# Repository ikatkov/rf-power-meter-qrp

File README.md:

# RF Power Meter QRP

This microcontroller-based RF power meter is tailored for Ham QRP, capable of measuring up to 6W. It offers power readings in two formats:

1. Milliwatts (mW) – displayed as a 4-digit value without decimals.
1. Decibel-milliwatts (dBm) – shown with one decimal place. Since the display lacks a dot, the reading appears as a 3-digit number (e.g., "123" represents 12.3 dBm).
1. Accuracy 0.4% @ 6W (+-25mW), 5% @ 10mW (+-0.5mW)

## Features

- Up to 6W RF power meter, assumes sin wave
- Peak power hold mode
- Compensated frequency resonse, less that 1.03 SWR 2-50MHz
- Power measurements in dBm and Watts on 4-digit LED display
- Support for multiple Ham frequency bands (3.7-50MHz)
- Calibrated and uses polynomial curve fitting for accurate measurements. Manually set frequency band in settings.
- Battery voltage monitoring and auto power-off after 5 minutes of inactivity. Press any button to reset.
- Vent holes on plastic enclosure have filters made of surgical mask fiber (anti dust for field operation)

## 2MHz - 50MHz

## 2MHz - 175MHz

## Hardware

Schematic - [PDF](schematic.pdf)

- Arduino-compatible microcontroller
- 4-digit+MHz symbol LED display (salavged from a car FM transmitter)
- RF didode detector circuit
- Power latch circuit for MCU driven turn off
- Buzzer for audio feedback
- External precision voltage reference 

## Usage

- **To Power On**: Flip the main (storage mode) switch to ON. Press and hold the OK button (lower) to power on. Device starts with battery voltage displayed, followed by the currently selected frequency band. 

- **Info Button** (top):
  - Single click: Toggle between dBm/Watts
  - Double click: Enter measurement mode selection. Use the same button to switch between modes **continious** (default) vs **hold peak** mode. Use OK button to confirm when done.
  - Long press: Enter frequency band selection. Use the same button to cycle through bands.Use OK button to confirm when done.
- **OK Button** (bottom):
  - Single click: When in main screen - resets to zero, in menu screens confirms selection and exit to the main screen.
  - Long press (2s): Powers off

## Technical Specifications

- Calibrated for Ham frequency bands: 3.7MHz, 7.2MHz, 14.2MHz, 18MHz, 21MHz, 24MHz, 28MHz, 50MHz 
- Accuracy 0.4% @ 6W (+-25mW), 5% @ 10mW (+-0.5mW)
- Min power level: 2mW (3dBm)
- Max power level: 6.3W (38dBm) in short burst, 4W continious
- Not temperature compensated
- Internal 500mAh battery, USB charged
- When powered off, 200uA current consumption. You can use storage mode switch to disconnect internal battery competely.

## Notes

Since it's a diode detector the only thing it can measure is peak voltage. Code inside assumes that input RF signal is a pure sine wave to make RF power calculations. 

### Frequency compensation

Leads and connector and other stray inductance skew 50Ω impedance, one good way to compensate is to add adjustanble shunt capacitance. Use VNA to adjust after pcb assembly.

[ltspice file](ltspice/qrt-rf-power-meter-shunt-cap-compensation.asc)

### DC supply filtering

Internal battery is nominal 3.7V, but the salvaged LCD screen needs 5V. There is boost DC-DC converter that gives 200mV ripple. There are two filters - one right after the converter, this goes to MCU. There is another one just before reference voltage goes to Aref pin.

[ltspice file](ltspice/power-ripple-filter.asc)

### Interface

The Salvaged FM LCD screen has two buttons, so I had to fallback to "click" vs "double-click" vs "long click" technique. The same button function differently depending in which mode device currently is - "main screen" vs "settings"

The screen itself has 4 digits and one dot. The dot is connected to "MHz" symbol. They always lit together.
Although I needed the dot for measurements, for example for dBms, I decided that showing "12.3 MHz" and claiming that this is "12.3 dBm" is rather akward. So the reading appears as a 3-digit number e.g. "123" represents 12.3 dBm. Watts reading always appear as 4 digit numbers with leading zeros as mW, "0123" reading represents 123mW. The dot and the "MHz" symbol come very handy when displaying frequency band. This setting is used to select which callibration curve to apply to the actual measurement.

Here is transition diagram:

```
                 ┌───────────────┐                   ┌─────────────┐
                 │ Cycle through ├───OK─button───────►  Saves to   │
                 │   Ham bands   │    click          │    NVRAM    │
                 └──────▲────────┘                   └───────┬─────┘
                        │                                    │      
                   info button                               │      
                     click                                   │      
                        │                                    │      
                 ┌──────┴────────┐                           │      
                 │Frequency band │                           │      
                 │  selection    │                           │      
                 │   screen      │                           │      
                 └───────────────┘                           │      
                       ▲ ▲                                   │      
                       │ │                                   │      
                       │ │                                   │      
                    info button                              │      
        ┌───────────long press─────────┐                     │      
        │                              │                     │      
        │                              │                     │      
        │                              │                     │      
┌───────┴───────┐              ┌───────┴───────┐             │      
│  Main screen  ├─info─button─►│  Main screen  │◄────────────┘      
│    mWatts     │◄──click──────┤     dBm       │◄────────────┐      
└───────┬───────┘              └───────┬───────┘             │      
        │                              │                     │      
        │                              │                     │      
        │                              │                     │      
        └──────────info button─────────┘                     │      
                   double│click                              │      
                      │  │                                   │      
                ┌─────▼──▼─────┐         When in the         │      
                │  Continious  │        "Hold Peak mode"     │      
                │     vs       │         display blinks      │      
                │  Hold peak   │                             │      
                └───────┬──────┘                             │      
                        │                                    │      
                   info button                               │      
                     click                                   │      
                        │                                    │      
                ┌───────▼─────────┐                          │      
                │  Cycle through  ├────OK─button─────────────┘      
                │    two modes    │     click                       
                └─────────────────┘                                                                                  
```                   

In any mode, long press on the "OK" button turns power off.

## License

[MIT License](LICENSE)

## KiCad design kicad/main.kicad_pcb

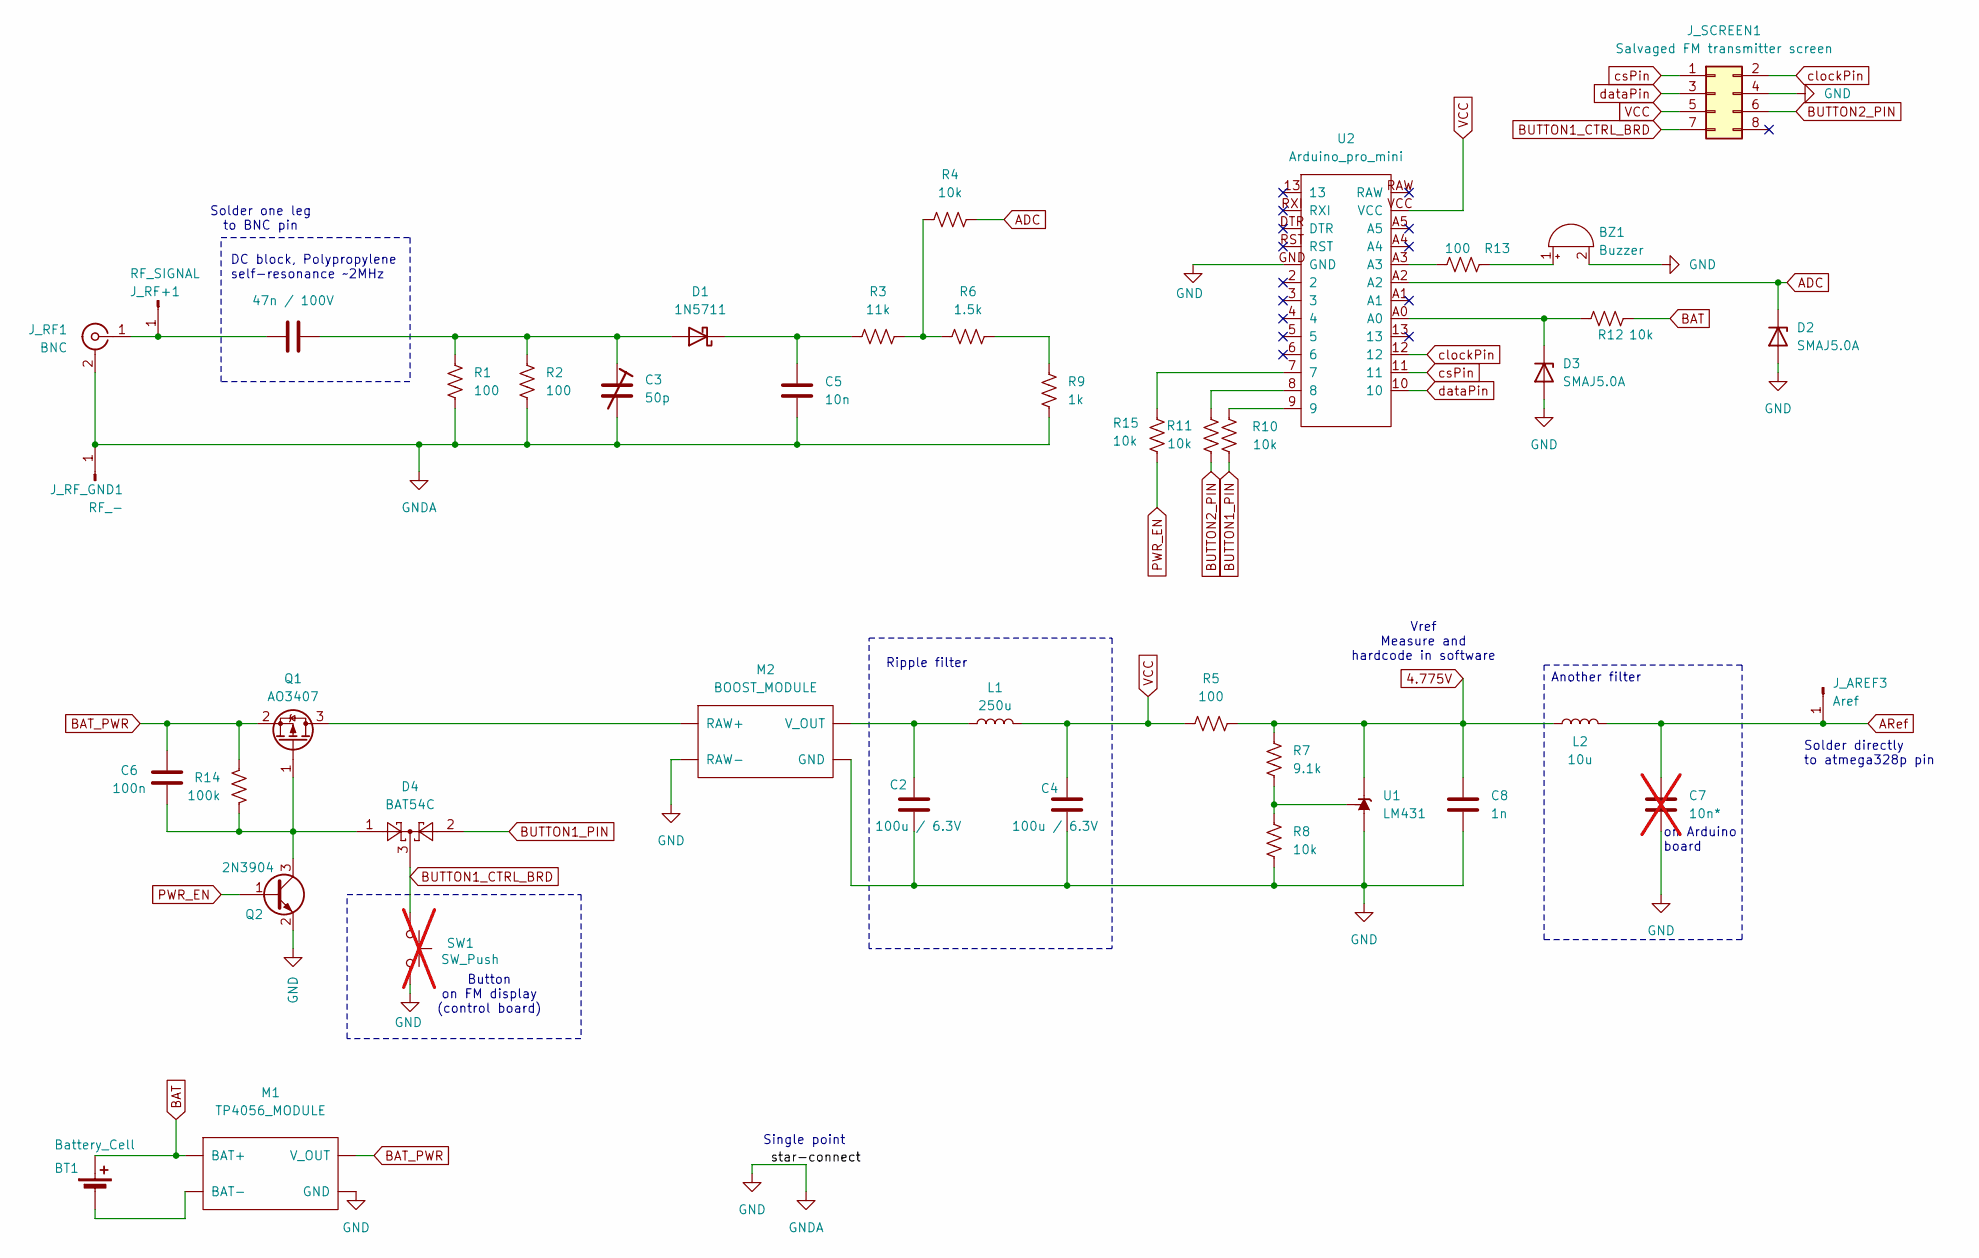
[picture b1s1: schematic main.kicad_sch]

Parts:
BT1: Battery_Cell
BZ1: Buzzer; Buzzer_12x9.5RM7.6
C1: 47n / 100V; C_Disc_D8.0mm_W2.5mm_P5.00mm
C2, C4: 100u / 6.3V; C_1206_3216Metric
C3: 50p; trimmer-capacitor-JML06
C5: 10n; C_1206_3216Metric
C6: 100n; C_1206_3216Metric
C7: 10n*; C_1206_3216Metric; not fitted
C8: 1n; C_1206_3216Metric
D1: 1N5711; D_DO-35_SOD27_P7.62mm_Horizontal
D2, D3: SMAJ5.0A; D_SMA
D4: BAT54C; SOT-23
J_AREF3: Aref; SolderWire-0.25sqmm_1x01_D0.65mm_OD2mm
J_RF1: BNC; SolderWire-1.5sqmm_1x01_D1.7mm_OD3.9mm
J_RF+1: RF_SIGNAL; SolderWire-1.5sqmm_1x01_D1.7mm_OD3.9mm
J_RF_GND1: RF_-; SolderWire-1.5sqmm_1x01_D1.7mm_OD3.9mm
J_SCREEN1: Salvaged FM transmitter screen; IDC-Header_2x04_P2.54mm_Vertical
L1: 250u; L_Bourns_SRN6045TA
L2: 10u; L_0805_2012Metric
M1: TP4056_MODULE; TP4056-18650
M2: BOOST_MODULE; boost-module
Q1: AO3407; SOT-23
Q2: 2N3904; SOT-23
R1, R2: 100; R_Axial_DIN0922_L20.0mm_D9.0mm_P25.40mm_Horizontal
R3: 11k; R_0805_2012Metric
R4, R8, R10, R11, R12, R15: 10k; R_0805_2012Metric
R5, R13: 100; R_0805_2012Metric
R6: 1.5k; R_0805_2012Metric
R7: 9.1k; R_0805_2012Metric
R9: 1k; R_0805_2012Metric
R14: 100k; R_0805_2012Metric
SW1: SW_Push; SW_Tactile_SPST_Angled_PTS645Vx31-2LFS; not fitted
U1: LM431; TO-92L_HandSolder
U2: Arduino_pro_mini; ARDUINO_PRO_MINI_NO_A5

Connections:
4.775V: C8.1, L2.1, R5.1, R7.1, U1.3 (K)
ADC: D2.1 (K), R4.2, U2.A2
ARef: C7.1, J_AREF3.1, L2.2
BAT: BT1.1 (+), M1.5 (BAT+), R12.1
BAT_PWR: C6.2, M1.3 (V_OUT), Q1.2 (S), R14.2
BUTTON1: D4.2, R10.2
BUTTON1_PIN: D4.3, J_SCREEN1.7, SW1.1
BUTTON2: J_SCREEN1.6, R11.2
GND: BZ1.2 (-), C2.2, C3.2, C4.2, C5.2, C7.2, C8.2, D2.2 (A), D3.2 (A), J_RF1.2 (Ext), J_RF_GND1.1, J_SCREEN1.4, M1.4 (GND), M2.1 (RAW-), M2.4 (GND), Q2.2 (E), R1.2, R2.2, R8.2, R9.2, SW1.2, U1.2 (A), U2.GND
unnamed: BZ1.1 (+), R13.1
unnamed: C1.2, C3.1, D1.2 (A), R1.1, R2.1
unnamed: C5.1, D1.1 (K), R3.1
unnamed: D3.1 (K), R12.2, U2.A0
unnamed: C1.1, J_RF1.1 (In), J_RF+1.1
unnamed: BT1.2 (-), M1.6 (BAT-)
unnamed: M2.2 (RAW+), Q1.3 (D)
unnamed: C2.1, L1.1, M2.3 (V_OUT)
unnamed: C6.1, D4.1, Q1.1 (G), Q2.3 (C), R14.1
unnamed: R3.2, R4.1, R6.2
unnamed: R6.1, R9.1
unnamed: R10.1, U2.9
unnamed: R11.1, U2.8
unnamed: R13.2, U2.A3
unnamed: R15.2, U2.7
unnamed: R7.2, R8.1, U1.1 (REF)
PWR_EN: Q2.1 (B), R15.1
VCC: C4.1, J_SCREEN1.5, L1.2, R5.2, U2.VCC
clockPin: J_SCREEN1.2, U2.12
csPin: J_SCREEN1.1, U2.11
dataPin: J_SCREEN1.3, U2.10

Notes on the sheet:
Ripple filter
Vref Measure and hardcode in software
Another filter
DC block, Polypropylene self-resonance ~2MHz
Button on FM display (control board)
Solder one leg to BNC pin
Single point
on Arduino board
Solder directly to atmega328p pin

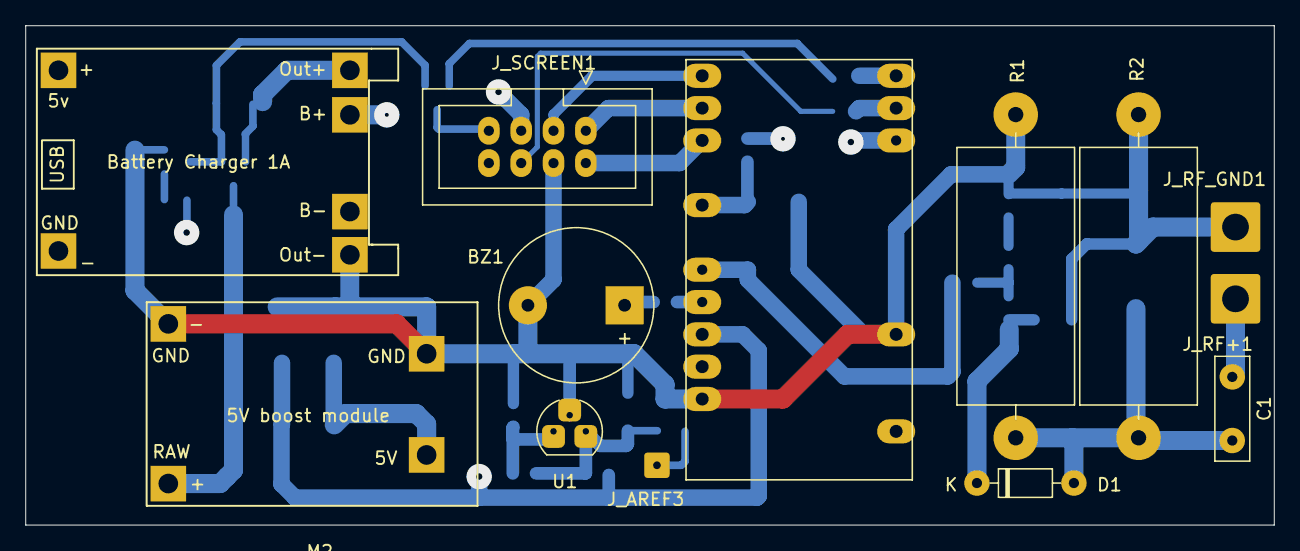
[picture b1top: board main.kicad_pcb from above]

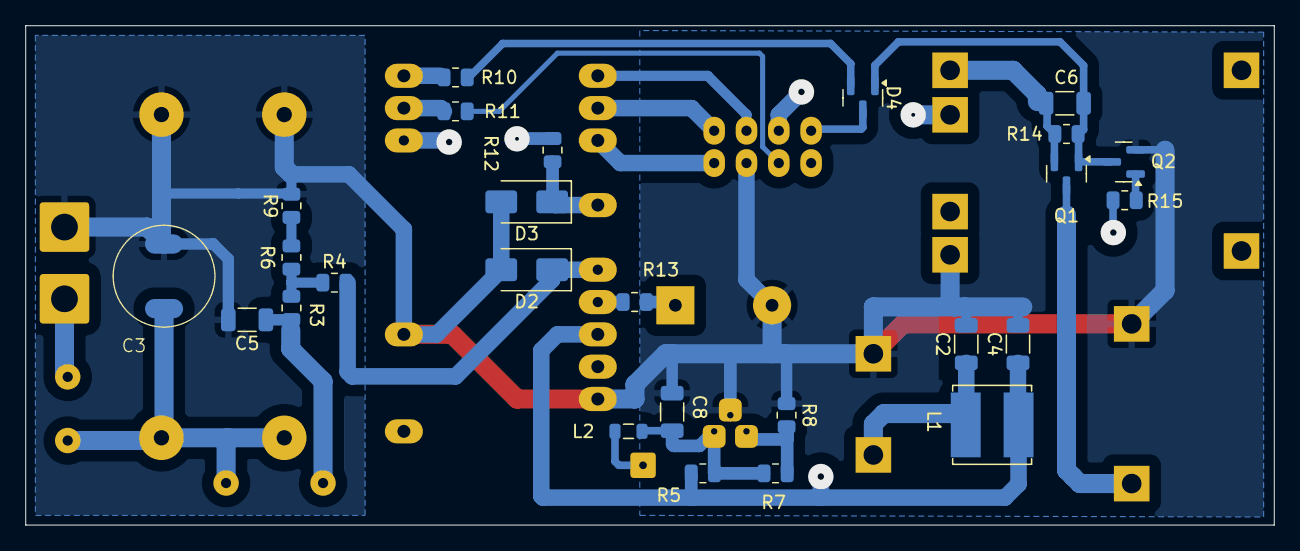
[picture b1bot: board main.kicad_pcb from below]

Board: 4 copper layers, 98.1 x 39.2 mm, 39 parts (26 on the bottom side), 29 nets.

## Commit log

2024-12-30 feat: Initial commit
2024-12-31 Add 3d model for enclosure
2024-12-31 Add python pre-req
2025-01-03 docs: clean up schematic and export to pdf and images
2025-01-03 docs: formatting
2025-01-03 docs: Update wording
2025-01-04 docs: More documentation
2025-01-04 fix: update ltspice
